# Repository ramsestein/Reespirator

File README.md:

# Reespirator 2020

Este repositorio pretende documentar y organizar los pasos para fabricar prototipos de  **Reespirator-2020**, un respirador open-source basado en el sistema de ventilación mecánica Jackson-Rees, diseñado y mejorado a partir de los prototipos elaborados por el equipo de Reesistencia Team para todas aquellas personas, organizaciones o empresas que quieran fabricarlo en cualquier parte del mundo.  

> ESTA DOCUMENTACIÓN ESTÁ EN ELABORACIÓN, COMPRUEBE REGULARMENTE LOS CAMBIOS, LAS PRIMERAS VERSIONES PUBLICADAS ESTÁN DESACTUALIZADAS. 

## Disclaimer
*Recuerde que un respirador es un dispositivo médico que sólo puede ser utilizado por personal cualificado y que un mal respirador o un respirador mal utilizado puede matar.*

La presente documentación **NO PERMITE CONSTRUIR UN RESPIRADOR FINAL**, sólo se publica para que se pueda fabricar PROTOTIPOS para investigación. 

## Info
*¿Qué es Reespirator 2020?*

El dispositivo Reespirator 2020 es un prototipo de sistema respirador de emergencia con elementos disponibles por la mayoría de las personas en cualquier parte del mundo, de rápida construcción y con la capacidad para mantener constantes ventilatorias aceptables en un paciente afecto de [Síndrome de Distrés Respiratorio Agudo](https://es.wikipedia.org/wiki/S%C3%ADndrome_de_dificultad_respiratoria_aguda) o SDRA que esperamos puede ser aplicable a los pacientes con COVID-19.

Aunque el origen de Reespirator es España, debido a las regulaciones y validaciones necesarias para los productos médicos, y aunque Reespirator 23 de [Reesistencia Team](https://gitlab.com/reesistencia), en el que se basó inicialmente este nuevo diseño, ha superado varias pruebas preclínicas con animales, y de compatibilidad electromagnética, suponemos que este dispositivo nunca se llegará a fabricar masivamente en España, dónde afortunadamente lo peor de la crisis del COVID-19 parece que ya ha pasado (08/04/20); esperamos que este y otros diseños puedan ser útiles en otros países.

Aún así no nos damos por vencidos y seguiremos desarrollando el proyecto al menos en 2 versiones:

* Versión low cost (basada en Arduino y con caja de metacrilato, madera...)
* Versión pro (con un autómata PLC + un HMI y caja de chapa plegada en acero inoxidable)

En la siguiente figura podemos ver una representación del dispositivo:

## Primeros pasos
**Antes de montar un respirador lea toda la documentación posible e infórmese bien, si necesita alguna aclaración abra un Issue y lo corregiremos en cuanto podamos. Si cree que puede mejorar el diseño, el código o que falta alguna cosa importante envíenos un Pull Request.**

## [Información médica básica del dispositivo Reespirator 2020](https://gitlab.com/reespirator/reespirator2020/-/blob/master/medical/MEDICAL.md)
El dispositivo se está diseñando para intentar cumplir las siguientes [especificaciones clínicas](https://foro.coronavirusmakers.org/index.php?p=/discussion/44/especificaciones-clinicas-de-un-respirador-util-en-esta-crisis#latest). Los dispositivos que estamos prototipando podrán funcionar en diferentes modos ventilatorios. En el siguiente enlace tendrás acceso a [Información médica básica sobre el dispositivo Reespirator 2020](https://gitlab.com/reespirator/reespirator2020/-/blob/master/medical/MEDICAL.md)

## [Estructura básica](https://gitlab.com/reespirator/reespirator2020/-/blob/master/case/CASE.md)
La versión low-cost de Reespirator 2020 consta de una [caja](https://gitlab.com/reespirator/reespirator2020/-/blob/master/case/CASE.md) diseñada para fabricarse mediante corte láser que contiene casi todos elementos del respirador en su interior. En el prototipo actual las piezas del prototipo se han diseñado para su corte por láser en metacrilato, si bien la imagen anterior corresponde a la nueva evolución que podrá fabricarse también con chapa plegada.

## [Sistema neumático](https://gitlab.com/reespirator/reespirator2020/-/blob/master/neumatic/NEUMATIC.md)
El [sistema neumático](https://gitlab.com/reespirator/reespirator2020/-/blob/master/neumatic/NEUMATIC.md) del Reespirator 2020 está basado en un sistema Jackson-Rees. Reespirator 2020 utiliza además una serie de válvulas, sensores de presión y caudal y tubuladuras para hacer llegar al aire a los pulmones del paciente.

## [Mecánica](https://gitlab.com/reespirator/reespirator2020/-/blob/master/mechanic/MECHANIC.md)
El [sistema mecánico](https://gitlab.com/reespirator/reespirator-doc/-/blob/master/mechanic/MECHANIC.md) pretende realizar los movimientos necesarios para realizar las maniobras de inspiración y espiración forzada del paciente mediante elementos mecánicos sustituyendo al personal humano que utilizaría el sistema de ventilación.

## [Electrónica](https://gitlab.com/reespirator/reespirator2020/-/blob/master/electronics/ELECTRONICS.md)
La [electrónica](https://gitlab.com/reespirator/reespirator-doc/-/blob/master/electronics/ELECTRONICS.md) de control gestiona el movimiento del motor y los sensores que permiten realizar un control de lazo cerrado automatizado del sistema.
Además de la electrónica de control se emplea una electrónica adicional como interfaz de usuario que permite monitorizar diferentes señales del respirador y modificar en tiempo real diferentes configuraciones del mismo.

## [Firmware](https://gitlab.com/reespirator/reespirator-doc/-/blob/master/firmware/FIRMWARE.md)
El sistema de control necesita ser programado con un [firmware](https://gitlab.com/reespirator/reespirator-doc/-/blob/master/firmware/FIRMWARE.md) que permita hacer funcionar el dispositivo. Dicho programa se ha realizado conforme a las especificaciones de los especialistas médicos para realizar las funciones para las que el dispositivo fue diseñado.

## [Simulación](https://gitlab.com/reespirator/reespirator2020/-/blob/master/simulation/SIMULATION.md)
En este apartado se consideran los fundamentos del sistema de control en lazo cerrado para los distintos modos de control que permite el Reespirator 2020. Los modelos matemáticos que permiten la [simulación numérica](https://gitlab.com/reespirasistemator/reespirator2020/-/blob/master/simulation/SIMULATION.md) del comportamiento del sistema corresponden a la información de este apartado.

## [Lista de materiales](https://gitlab.com/reespirator/reespirator2020/-/blob/master/bom/BOM.md)
La [lista de materiales, (BOM o Bill of materials)](https://gitlab.com/reespirator/reespirator2020/-/blob/master/bom/BOM.md) para construir un Reespirator 2020 es cuando menos complicada, incluye elementos como metacrilato, madera, MDF o chapa para la caja, sistmeas electrónicos como un Arduino Mega o un autómata PLC, y otros componentes, pero también elementos mecánicos y otros incluso impresos en 3D; pero sobre todo requiere también de la utilización de sistemas médicos tales como tubuladuras y un sistema ventilatorio Jackson-Rees.

## [Manual de usuario](https://gitlab.com/reespirator/reespirator2020/-/blob/master/manual/MANUAL.md)
El dispositivo Reespirator 2020 es un dispositivo médico y su uso sólo debe realizarse por personal especializado. Ofrecemos aquí un breve [manual de uso](https://gitlab.com/reespirator/reespirator-doc/-/blob/master/manual/MANUAL.md) del mismo; pero es el personal sanitario el que sabe los parámetros que deben utilizarse para el tratamiento de un paciente.

## [Vídeos]
En el siguiente enlace podemos ver algunos vídeos con detalles del Reespirator 2020 en funcionamiento:

* https://www.youtube.com/channel/UC9xr1HbWGLBjd4ADTvGcOnw

## Historia y principales cambios de esta versión

El proyecto Reespirator2020 toma como punto de partida el proyecto Reespirator 23 (o 24) v3 de **Reesistencia Team** a partir del cual realizamos un fork, el repositorio original está en [https://gitlab.com/reesistencia](https://gitlab.com/reesistencia).

En esta nueva versión se incluyen principalmente los siguientes cambios:

 - Revisión y reestructuración en profundidad del códido de Arduino para asegurar la robustez de funcionamiento en todos los supuestos.
 - La recuperación del interfaz básico con LCD de 20x04 y elementos sencillos de control (4 pulsadores y un encoder con pulsador).
 - Establecimiento y documentación de una interfaz de comunicación serie que permite la utilización de sistemas (en adelante llamados Display+) de visualización, control y conectividad, que pueden ser utilizados como accesorios para aportar mejor usabilidad al sistema.
 - Se trabaja para estandarizar y popularizar los sensores y electro-válvulas para utilizar partes (comerciales o diseñadas) posibles de conseguir con la situación de emergencia actual y a precios accesibles.
 - Posibilidad de usar diferentes interfaces de usuario.
 - Opción de utilizar un microcontrolador tipo Arduino o similar o bien un autómata PLC.

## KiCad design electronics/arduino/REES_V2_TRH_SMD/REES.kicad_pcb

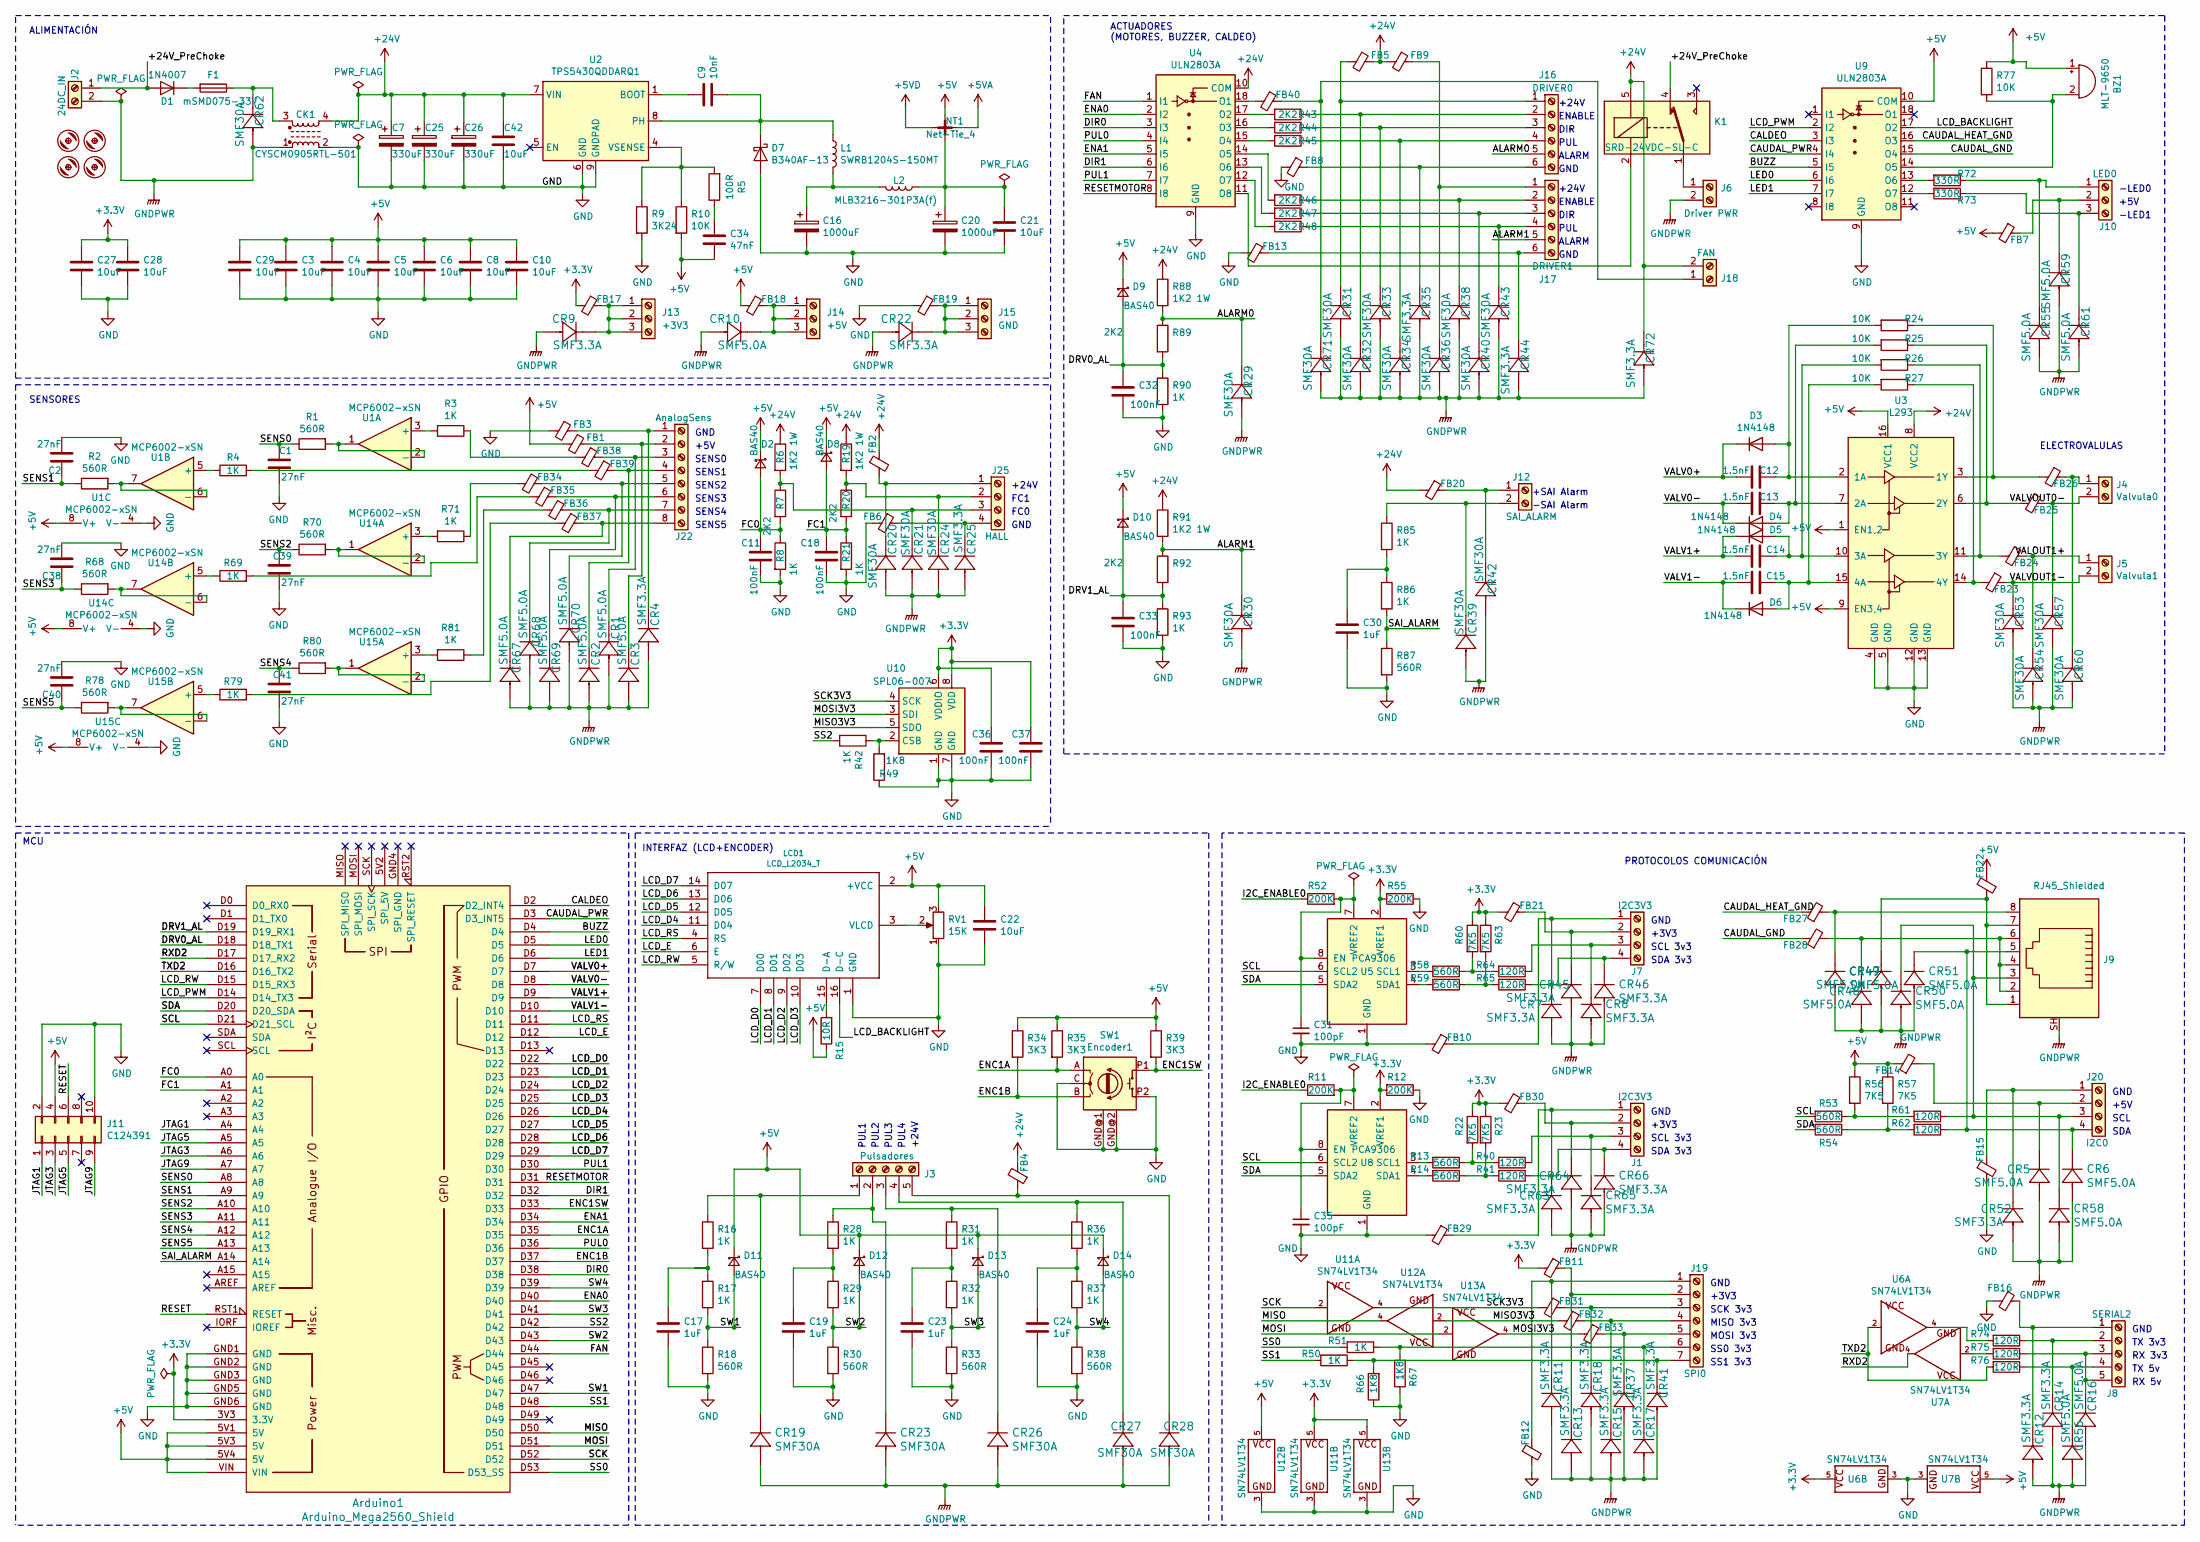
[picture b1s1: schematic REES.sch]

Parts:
Arduino1: Arduino_Mega2560_Shield
BZ1: MLT-9650; Buzzer_CUI_CPT-9019S-SMT
C1, C2, C38, C39, C40, C41: 27nF; C_0603_1608Metric
C3, C4, C5, C6, C8, C10, C21, C22, C27, C28, C29, C42: 10uF; C_1206_3216Metric
C7, C25, C26: 330uF; CP_Elec_10x10.5
C9: 10nF; C_0603_1608Metric
C11, C18, C32, C33, C36, C37: 100nF; C_0603_1608Metric
C12, C13, C14, C15: 1.5nF; C_0603_1608Metric
C16, C20: 1000uF; CP_Elec_10x10.5
C17, C19, C23, C24, C30: 1uF; C_0603_1608Metric
C31, C35: 100pF; C_0603_1608Metric
C34: 47nF; C_0603_1608Metric
CK1: CYSCM0905RTL-501; L_CommonMode_Wuerth_WE-SL2
CR1, CR2, CR3, CR5, CR6, CR10, CR16, CR47, CR48, CR49, CR50, CR51, CR55, CR56, CR58, CR59, CR61, CR67, CR68, CR69, CR70: SMF5.0A; D_SOD-123F
CR4, CR7, CR8, CR9, CR11, CR12, CR13, CR14, CR15, CR17, CR18, CR22, CR25, CR35, CR37, CR41, CR44, CR45, CR46, CR52, CR63, CR64, CR65, CR66, CR72: SMF3.3A; D_SOD-123F
CR19, CR20, CR21, CR23, CR24, CR26, CR27, CR28, CR29, CR30, CR31, CR32, CR33, CR34, CR36, CR38, CR39, CR40, CR42, CR43, CR53, CR54, CR57, CR60, CR62, CR71: SMF30A; D_SOD-123F
D1: 1N4007; D_SMA
D2, D8, D9, D10, D11, D12, D13, D14: BAS40; D_SOT-23_ANK
D3, D4, D5, D6: 1N4148; D_SOD-123
D7: B340AF-13; D_SMA
F1: mSMD075-33V; Fuse_1812_4532Metric
FB1, FB2, FB3, FB4, FB5, FB6, FB7, FB8, FB9, FB10, FB11, FB12, FB13, FB14, FB15, FB16, FB17, FB18, FB19, FB20, FB21, FB22, FB23, FB24, FB25, FB26, FB27, FB28, FB29, FB30, FB31, FB32, FB33, FB34, FB35, FB36, FB37, FB38, FB39, FB40: MLB3216-301P3A(f); C_1206_3216Metric
H1, H2, H3, H4: HOLES_MOUNT-HOLE3.6; HOLES_3,6
J1, J7: I2C3V3; TerminalBlock_Phoenix_MKDS-3-4-5.08_1x04_P5.08mm_Horizontal
J2: 24DC_IN; TerminalBlock_Phoenix_MKDS-3-2-5.08_1x02_P5.08mm_Horizontal
J3: Pulsadores; TerminalBlock_Phoenix_MKDS-3-5-5.08_1x05_P5.08mm_Horizontal
J4: Valvula0; TerminalBlock_Phoenix_MKDS-3-2-5.08_1x02_P5.08mm_Horizontal
J5: Valvula1; TerminalBlock_Phoenix_MKDS-3-2-5.08_1x02_P5.08mm_Horizontal
J6: Driver PWR; TerminalBlock_Phoenix_MKDS-3-2-5.08_1x02_P5.08mm_Horizontal
J8: SERIAL2; TerminalBlock_Phoenix_MKDS-3-5-5.08_1x05_P5.08mm_Horizontal
J9: RJ45_Shielded; RJ45_Hanrun_HR911105A
J10: LED0; TerminalBlock_Phoenix_MKDS-3-3-5.08_1x03_P5.08mm_Horizontal
J11: C124391; PinHeader_2x05_P2.54mm_Vertical_SMD
J12: SAI_ALARM; TerminalBlock_Phoenix_MKDS-3-2-5.08_1x02_P5.08mm_Horizontal
J13: +3V3; TerminalBlock_Phoenix_MKDS-3-3-5.08_1x03_P5.08mm_Horizontal
J14: +5V; TerminalBlock_Phoenix_MKDS-3-3-5.08_1x03_P5.08mm_Horizontal
J15: GND; TerminalBlock_Phoenix_MKDS-3-3-5.08_1x03_P5.08mm_Horizontal
J16: DRIVER0; TerminalBlock_Phoenix_MKDS-3-6-5.08_1x06_P5.08mm_Horizontal
J17: DRIVER1; TerminalBlock_Phoenix_MKDS-3-6-5.08_1x06_P5.08mm_Horizontal
J18: FAN; TerminalBlock_Phoenix_MKDS-3-2-5.08_1x02_P5.08mm_Horizontal
J19: SPI0; TerminalBlock_Phoenix_MKDS-3-7-5.08_1x07_P5.08mm_Horizontal
J20: I2C0; TerminalBlock_Phoenix_MKDS-3-4-5.08_1x04_P5.08mm_Horizontal
J22: AnalogSens; TerminalBlock_Phoenix_MKDS-3-8-5.08_1x08_P5.08mm_Horizontal
J25: HALL; TerminalBlock_Phoenix_MKDS-3-4-5.08_1x04_P5.08mm_Horizontal
K1: SRD-24VDC-SL-C; Relay_SPDT_Omron-G5LE-1
L1: SWRB1204S-150MT; L_Bourns_SRR1210A
L2: MLB3216-301P3A(f); C_1206_3216Metric
LCD1: LCD_L2034_T; L2034-T
NT1: Net-Tie_4; NetTie-4_SMD_Pad0.5mm
R1, R2, R13, R14, R18, R30, R33, R38, R53, R54, R58, R59, R68, R70, R78, R80, R87: 560R; R_0805_2012Metric
R3, R4, R8, R16, R17, R21, R28, R29, R31, R32, R36, R37, R42, R50, R51, R69, R71, R79, R81, R85, R86, R90, R93: 1K; R_1206_3216Metric
R5: 100R; R_0805_2012Metric
R6, R19, R88, R91: 1K2 1W; R_2512_6332Metric
R7, R20, R43, R44, R45, R46, R47, R48, R89, R92: 2K2; R_1206_3216Metric
R9: 3K24; R_0603_1608Metric
R10, R77: 10K; R_0603_1608Metric
R11, R12, R52, R55: 200K; R_0603_1608Metric
R15: 10R; R_1206_3216Metric
R22, R23, R56, R57, R60, R63: 7K5; R_0603_1608Metric
R24, R25, R26, R27: 10K; R_0805_2012Metric
R34, R35: 3K3; R_0603_1608Metric
R39: 3K3; R_0805_2012Metric
R40, R41, R61, R62, R64, R65, R74, R75, R76: 120R; R_1206_3216Metric
R49, R66, R67: 1K8; R_1206_3216Metric
R72, R73: 330R; R_0805_2012Metric
RV1: 15K; Potentiometer_Bourns_3214W_Vertical
SW1: Encoder1; PEC12_INCREMENTAL_ENCODER
U1, U14, U15: MCP6002-xSN; SOIC-8_3.9x4.9mm_P1.27mm
U2: TPS5430QDDARQ1; TI_SO-PowerPAD-8_ThermalVias
U3: L293; DIP-16_W7.62mm
U4, U9: ULN2803A; SOIC-18W_7.5x11.6mm_P1.27mm
U5, U8: PCA9306; TSSOP-8_3x3mm_P0.65mm
U6, U7, U11, U12, U13: SN74LV1T34; SOT-23-5_HandSoldering
U10: SPL06-007; Bosch_LGA-8_2x2.5mm_P0.65mm_ClockwisePinNumbering

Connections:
+3V3: Arduino1.3V3 (3.3V), C27.1, C28.1, C36.1, C37.1, FB11.2, FB17.2, FB21.2, FB30.2, R12.2, R22.1, R23.1, R55.2, R60.1, R63.1, U5.2 (VREF1), U6.5 (P$V+), U8.2 (VREF1), U10.6 (VDDIO), U10.8 (VDD), U11.5 (P$V+), U13.5 (P$V+)
+5V: Arduino1.5V1 (5V), Arduino1.5V3 (5V), Arduino1.5V4 (5V), Arduino1.VIN, BZ1.1 (-), C3.1, C4.1, C5.1, C6.1, C8.1, C10.1, C22.1, C29.1, C34.2, D2.1 (K), D8.1 (K), D9.1 (K), D10.1 (K), D11.1 (K), D12.1 (K), D13.1 (K), D14.1 (K), FB1.2, FB7.2, FB14.1, FB18.2, FB22.1, J11.4, LCD1.2 (+VCC), NT1.3, R10.2, R15.1, R34.1, R35.1, R39.1, R56.1, R57.1, R77.1, RV1.3, U1.8 (V+), U3.1 (EN1,2), U3.9 (EN3,4), U3.16 (VCC1), U7.5 (P$V+), U9.10 (COM), U12.5 (P$V+), U14.8 (V+), U15.8 (V+)
+24V: C7.1, C25.1, C26.1, C42.1, CK1.4, CR72.1, FB2.1, FB4.2, FB5.1, FB9.2, FB20.2, J18.2, K1.5, R6.1, R19.1, R88.1, R91.1, U2.7 (VIN), U3.8 (VCC2), U4.10 (COM)
/+24V_PreChoke: D1.2 (A), J2.1, K1.4
/ALARM0: CR29.1, J16.5, R88.2, R89.1
/ALARM1: CR30.1, J17.5, R91.2, R92.1
/BUZZ: Arduino1.D4, U9.5 (I5)
/CALDEO: Arduino1.D2 (D2_INT4), U9.3 (I3)
/CAUDAL_GND: FB28.1, U9.15 (O4)
/CAUDAL_HEAT_GND: FB27.1, U9.16 (O3)
/CAUDAL_PWR: Arduino1.D3 (D3_INT5), U9.4 (I4)
/DIR0: Arduino1.D38, U4.3 (I3)
/DIR1: Arduino1.D32, U4.6 (I6)
/DRV0_AL: Arduino1.D18 (D18_TX1), C32.1, D9.2 (A), R89.2, R90.1
/DRV1_AL: Arduino1.D19 (D19_RX1), C33.1, D10.2 (A), R92.2, R93.1
/ENA0: Arduino1.D40, U4.2 (I2)
/ENA1: Arduino1.D34, U4.5 (I5)
/ENC1A: Arduino1.D35, R35.2, SW1.A
/ENC1B: Arduino1.D37, R34.2, SW1.B
/ENC1SW: Arduino1.D33, R39.2, SW1.P1
/FAN: Arduino1.D44, U4.1 (I1)
/FC0: Arduino1.A0, C11.1, D2.2 (A), R7.2, R8.1
/FC1: Arduino1.A1, C18.1, D8.2 (A), R20.2, R21.1
/I2C_ENABLE0: R11.1, R52.1
/JTAG1: Arduino1.A4, J11.1
/JTAG3: Arduino1.A6, J11.3
/JTAG5: Arduino1.A5, J11.5
/JTAG9: Arduino1.A7, J11.9
/LCD_BACKLIGHT: LCD1.16 (D-C), U9.17 (O2)
/LCD_D0: Arduino1.D22, LCD1.7 (D00)
/LCD_D1: Arduino1.D23, LCD1.8 (D01)
/LCD_D2: Arduino1.D24, LCD1.9 (D02)
/LCD_D3: Arduino1.D25, LCD1.10 (D03)
/LCD_D4: Arduino1.D26, LCD1.11 (D04)
/LCD_D5: Arduino1.D27, LCD1.12 (D05)
/LCD_D6: Arduino1.D28, LCD1.13 (D06)
/LCD_D7: Arduino1.D29, LCD1.14 (D07)
/LCD_E: Arduino1.D12, LCD1.6 (E)
/LCD_PWM: Arduino1.D14 (D14_TX3), U9.2 (I2)
/LCD_RS: Arduino1.D11, LCD1.4 (RS)
/LCD_RW: Arduino1.D15 (D15_RX3), LCD1.5 (R/W)
/LED0: Arduino1.D5, U9.6 (I6)
/LED1: Arduino1.D6, U9.7 (I7)
/MISO: Arduino1.D50, U12.4 (Y)
/MISO3V3: FB32.2, U10.5 (SDO), U12.2 (A)
/MOSI: Arduino1.D51, U13.2 (A)
/MOSI3V3: FB33.2, U10.3 (SDI), U13.4 (Y)
/PUL0: Arduino1.D36, U4.4 (I4)
/PUL1: Arduino1.D30, U4.7 (I7)
/RESET: Arduino1.RST1 (RESET), J11.6
/RESETMOTOR: Arduino1.D31, U4.8 (I8)
/RXD2: Arduino1.D17 (D17_RX2), U7.4 (Y)
/SAI_ALARM: Arduino1.A14, R86.2, R87.1
/SCK: Arduino1.D52, U11.2 (A)
/SCK3V3: FB31.2, U10.4 (SCK), U11.4 (Y)
/SCL: Arduino1.D21 (D21_SCL), R53.2, U5.6 (SCL2), U8.6 (SCL2)
/SDA: Arduino1.D20 (D20_SDA), R54.2, U5.5 (SDA2), U8.5 (SDA2)
/SENS0: Arduino1.A8, C1.1, R1.1
/SENS1: Arduino1.A9, C2.1, R2.1
/SENS2: Arduino1.A10, C39.1, R70.1
/SENS3: Arduino1.A11, C38.1, R68.1
/SENS4: Arduino1.A12, C41.1, R80.1
/SENS5: Arduino1.A13, C40.1, R78.1
/SS0: Arduino1.D53 (D53_SS), R51.2
/SS1: Arduino1.D48, R50.2
/SS2: Arduino1.D42, R42.2
/SW1: Arduino1.D47, D11.2 (A), R17.2, R18.1
/SW2: Arduino1.D43, D12.2 (A), R29.2, R30.1
/SW3: Arduino1.D41, D13.2 (A), R32.2, R33.1
/SW4: Arduino1.D39, D14.2 (A), R37.2, R38.1
/TXD2: Arduino1.D16 (D16_TX2), R76.2, U6.2 (A)
/VALOUT1+: CR54.1, FB24.1, J5.1
/VALV0+: Arduino1.D7, C12.2, D3.1 (K)
/VALV0-: Arduino1.D8, C13.2, D4.1 (K)
/VALV1+: Arduino1.D9, C14.2, D5.1 (K)
/VALV1-: Arduino1.D10, C15.2, D6.1 (K)
/VALVOUT0-: CR57.1, FB25.1, J4.2
/VALVOUT1-: CR53.1, FB23.1, J5.2
GND: Arduino1.GND1 (GND), Arduino1.GND2 (GND), Arduino1.GND3 (GND), Arduino1.GND5 (GND), Arduino1.GND6 (GND), C1.2, C2.2, C3.2, C4.2, C5.2, C6.2, C7.2, C8.2, C10.2, C11.2, C16.2, C17.2, C18.2, C19.2, C20.2, C21.2, C22.2, C23.2, C24.2, C25.2, C26.2, C27.2, C28.2, C29.2, C30.2, C31.2, C32.2, C33.2, C35.2, C36.2, C37.2, C38.2, C39.2, C40.2, C41.2, C42.2, CK1.2, D7.2 (A), FB3.2, FB6.2, FB8.2, FB10.2, FB12.2, FB13.2, FB15.2, FB16.2, FB19.2, FB29.2, J11.2, J11.10, LCD1.1 (GND), R8.2, R9.2, R12.1, R18.2, R21.2, R30.2, R33.2, R38.2, R49.1, R55.1, R66.1, R67.1, R87.2, R90.2, R93.2, RV1.1, SW1.C, SW1.GND@1, SW1.GND@2, SW1.P2, U1.4 (V-), U2.6 (GND), U2.9 (GNDPAD), U3.4 (GND), U3.5 (GND), U3.12 (GND), U3.13 (GND), U4.9 (GND), U5.1 (GND), U6.3 (P$V-), U7.3 (P$V-), U8.1 (GND), U9.9 (GND), U10.1 (GND), U10.7 (GND), U11.3 (P$V-), U12.3 (P$V-), U13.3 (P$V-), U14.4 (V-), U15.4 (V-)
GNDPWR: CK1.1, CR1.2, CR2.2, CR3.2, CR4.2, CR5.2, CR6.2, CR7.2, CR8.2, CR9.2, CR10.2, CR11.2, CR12.2, CR13.2, CR14.2, CR15.2, CR16.2, CR17.2, CR18.2, CR19.2, CR20.2, CR21.2, CR22.2, CR23.2, CR24.2, CR25.2, CR26.2, CR27.2, CR28.2, CR29.2, CR30.2, CR31.2, CR32.2, CR33.2, CR34.2, CR35.2, CR36.2, CR37.2, CR38.2, CR39.2, CR40.2, CR41.2, CR42.2, CR43.2, CR44.2, CR45.2, CR46.2, CR47.2, CR48.2, CR49.2, CR50.2, CR51.2, CR52.2, CR53.2, CR54.2, CR55.2, CR56.2, CR57.2, CR58.2, CR59.2, CR60.2, CR61.2, CR62.2, CR63.2, CR64.2, CR65.2, CR66.2, CR67.2, CR68.2, CR69.2, CR70.2, CR71.2, CR72.2, J2.2, J6.2, J9.SH
unnamed: BZ1.2 (+), R77.2, U9.14 (O5)
unnamed: C9.1, U2.1 (BOOT)
unnamed: C9.2, D7.1 (K), L1.1, U2.8 (PH)
unnamed: C12.1, D3.2 (A), R24.2, U3.2 (1A)
unnamed: C13.1, D4.2 (A), R25.2, U3.7 (2A)
unnamed: C14.1, D5.2 (A), R26.2, U3.10 (3A)
unnamed: C15.1, D6.2 (A), R27.2, U3.15 (4A)
unnamed: C16.1, L1.2, L2.2
unnamed: C17.1, R16.2, R17.1
unnamed: C19.1, R28.2, R29.1
unnamed: C20.1, C21.1, L2.1, NT1.4
unnamed: C23.1, R31.2, R32.1
unnamed: C24.1, R36.2, R37.1
unnamed: C30.1, R85.2, R86.1
unnamed: C31.1, R52.2, U5.7 (VREF2), U5.8 (EN)
unnamed: C34.1, R5.1
unnamed: C35.1, R11.2, U8.7 (VREF2), U8.8 (EN)
unnamed: CK1.3, CR62.1, F1.1
unnamed: CR1.1, FB38.1, J22.3
unnamed: CR2.1, FB39.1, J22.4
unnamed: CR3.1, FB1.1, J22.2
unnamed: CR4.1, FB3.1, J22.1
unnamed: CR5.1, FB14.2, J20.2
unnamed: CR8.1, J7.3, R64.1
unnamed: CR9.1, FB17.1, J13.1, J13.2, J13.3
unnamed: CR10.1, FB18.1, J14.1, J14.2, J14.3
unnamed: CR11.1, FB12.1, J19.1
unnamed: CR12.1, FB16.1, J8.1
unnamed: CR13.1, FB11.1, J19.2
unnamed: CR14.1, J8.2, R74.1
unnamed: CR15.1, FB32.1, J19.4
unnamed: CR16.1, J8.3, J8.5, R75.1
unnamed: CR17.1, J19.6, R51.1, R67.2
unnamed: CR18.1, FB31.1, J19.3
unnamed: CR19.1, J3.1, R16.1
unnamed: CR20.1, FB2.2, J25.1
unnamed: CR21.1, J25.3, R6.2, R7.1
unnamed: CR22.1, FB19.1, J15.1, J15.2, J15.3
unnamed: CR23.1, J3.2, R28.1
unnamed: CR24.1, J25.2, R19.2, R20.1
unnamed: CR25.1, FB6.1, J25.4
unnamed: CR26.1, J3.3, R31.1
unnamed: CR27.1, J3.4, R36.1
unnamed: CR28.1, FB4.1, J3.5
unnamed: CR31.1, FB5.2, J16.1
unnamed: CR32.1, J16.2, R43.1
unnamed: CR33.1, J16.3, R44.1
unnamed: CR34.1, J16.4, R45.1
unnamed: CR35.1, FB8.1, J16.6
unnamed: CR36.1, FB9.1, J17.1
unnamed: CR37.1, FB33.1, J19.5
unnamed: CR38.1, J17.2, R46.1
unnamed: CR39.1, J12.2, R85.1
unnamed: CR40.1, J17.3, R47.1
unnamed: CR41.1, J19.7, R50.1, R66.2
unnamed: CR42.1, FB20.1, J12.1
unnamed: CR43.1, J17.4, R48.1
unnamed: CR44.1, FB13.1, J17.6
unnamed: CR45.1, FB21.1, J7.2
unnamed: CR7.1, CR46.1, FB10.1, J7.1, J7.4, R65.1
unnamed: CR47.1, FB27.2, J9.8
unnamed: CR48.1, FB28.2, J9.2, J9.4, J9.6
unnamed: CR49.1, FB22.2, J9.1, J9.7
unnamed: CR50.1, CR58.1, J9.3, J20.3, R61.1
unnamed: CR6.1, CR51.1, J9.5, J20.4, R62.1
unnamed: CR52.1, FB15.1, J20.1
unnamed: CR55.1, J10.1, R72.1
unnamed: CR56.1, J8.4, R76.1
unnamed: CR59.1, FB7.1, J10.2
unnamed: CR60.1, FB26.1, J4.1
unnamed: CR61.1, J10.3, R73.1
unnamed: CR63.1, CR66.1, FB29.1, J1.1, J1.4, R41.1
unnamed: CR64.1, FB30.1, J1.2
unnamed: CR65.1, J1.3, R40.1
unnamed: CR67.1, FB37.1, J22.8
unnamed: CR68.1, FB36.1, J22.7
unnamed: CR69.1, FB35.1, J22.6
unnamed: CR70.1, FB34.1, J22.5
unnamed: CR71.1, FB40.1, J18.1
unnamed: D1.1 (K), F1.2
unnamed: FB23.2, R27.1, U3.14 (4Y)
unnamed: FB24.2, R26.1, U3.11 (3Y)
unnamed: FB25.2, R25.1, U3.6 (2Y)
unnamed: FB26.2, R24.1, U3.3 (1Y)
unnamed: FB34.2, R71.1
unnamed: FB35.2, R69.2
unnamed: FB36.2, R81.1
unnamed: FB37.2, R79.2
unnamed: FB38.2, R3.1
unnamed: FB39.2, R4.2
unnamed: FB40.2, U4.18 (O1)
unnamed: J6.1, K1.1
unnamed: K1.2, U4.11 (O8)
unnamed: LCD1.3 (VLCD), RV1.2
unnamed: LCD1.15 (D-A), R15.2
unnamed: R1.2, U1.1, U1.2 (-)
unnamed: R2.2, U1.6 (-), U1.7
unnamed: R3.2, U1.3 (+)
unnamed: R4.1, U1.5 (+)
unnamed: R5.2, R9.1, R10.1, U2.4 (VSENSE)
unnamed: R13.1, R22.2, R40.2
unnamed: R13.2, U8.3 (SCL1)
unnamed: R14.1, R23.2, R41.2
unnamed: R14.2, U8.4 (SDA1)
unnamed: R42.1, R49.2, U10.2 (CSB)
unnamed: R43.2, U4.17 (O2)
unnamed: R44.2, U4.16 (O3)
unnamed: R45.2, U4.15 (O4)
unnamed: R46.2, U4.14 (O5)
unnamed: R47.2, U4.13 (O6)
unnamed: R48.2, U4.12 (O7)
unnamed: R53.1, R56.2, R61.2
unnamed: R54.1, R57.2, R62.2
unnamed: R58.1, R60.2, R64.2
unnamed: R58.2, U5.3 (SCL1)
unnamed: R59.1, R63.2, R65.2
unnamed: R59.2, U5.4 (SDA1)
unnamed: R68.2, U14.6 (-), U14.7
unnamed: R69.1, U14.5 (+)
unnamed: R70.2, U14.1, U14.2 (-)
unnamed: R71.2, U14.3 (+)
unnamed: R72.2, U9.13 (O6)
unnamed: R73.2, U9.12 (O7)
unnamed: R74.2, U6.4 (Y)
unnamed: R75.2, U7.2 (A)
unnamed: R78.2, U15.6 (-), U15.7
unnamed: R79.1, U15.5 (+)
unnamed: R80.2, U15.1, U15.2 (-)
unnamed: R81.2, U15.3 (+)

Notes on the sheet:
ALIMENTACIÓN
ACTUADORES (MOTORES, BUZZER, CALDEO)
SENSORES
PROTOCOLOS COMUNICACIÓN
MCU
ELECTROVALULAS
RX 5v
TX 5v
TX 3v3
GND
-SAI Alarm
+SAI Alarm
RX 3v3
SCL 3v3
SDA 3v3
+3V3
SDA
+5V
SCL
PUL
ENABLE
+24V
DIR
ALARM
-LED0
-LED1
PUL3
PUL1
PUL2
PUL4
SCK 3v3
MISO 3v3
MOSI 3v3
SS0 3v3
SS1 3v3
SENS1
SENS0
FC0
FC1
INTERFAZ (LCD+ENCODER)

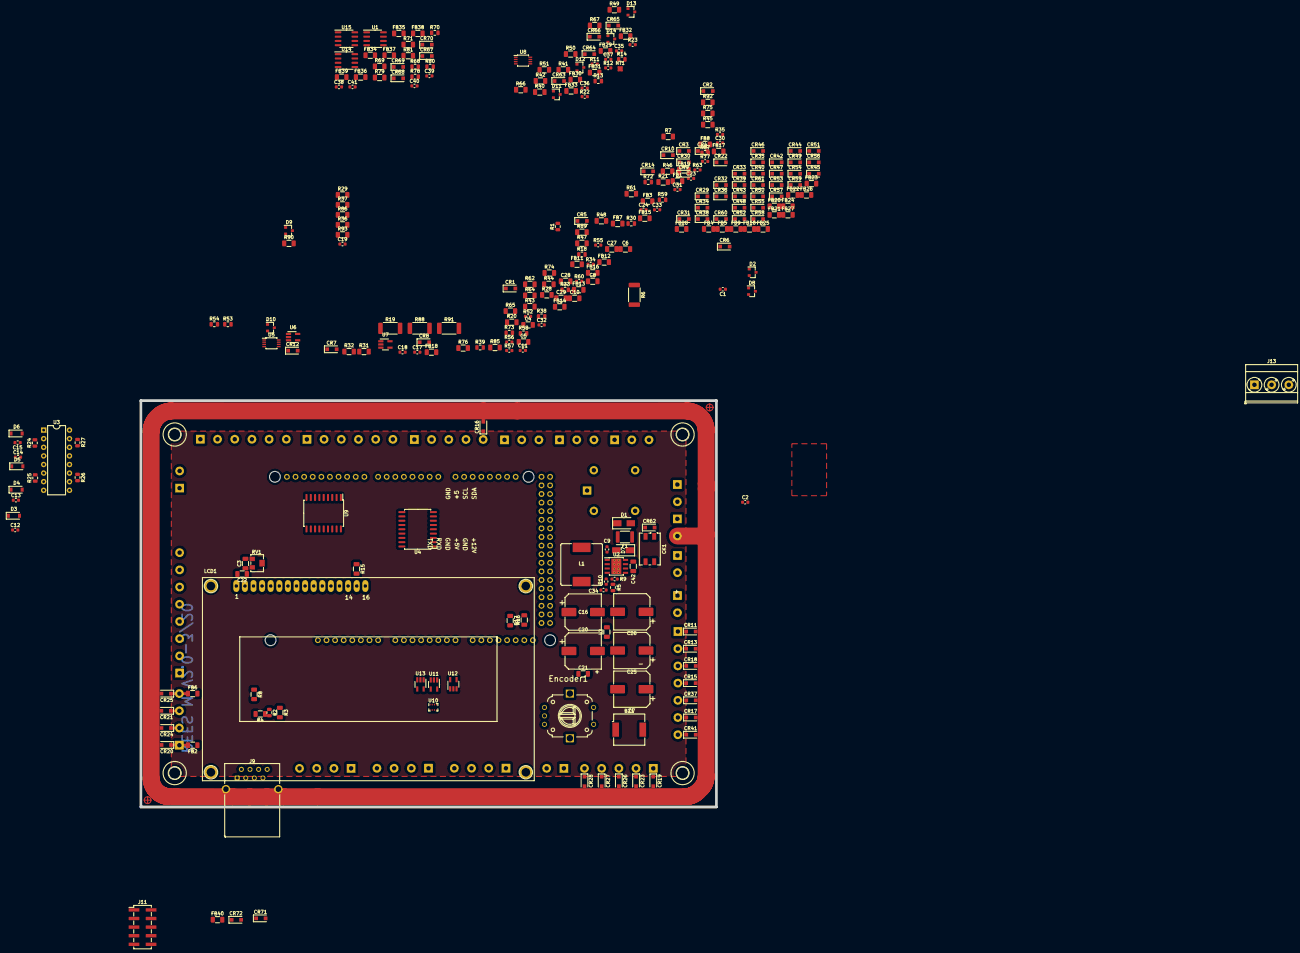
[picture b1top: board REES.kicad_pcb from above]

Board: 2 copper layers, 170.0 x 120.0 mm, 310 parts (0 on the bottom side), 209 nets.

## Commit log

2020-04-14 Update electronics/arduino/diagrama_bloques_esquema.md, images/diagrama_bloques_esquema.png, alimentacion_esquema.md, electronics/arduino/alimentacion_esquema.md, electronics/arduino/mcu_esquema.md, 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
2020-04-14 Montaje de la caja en metacrilato
2020-04-14 tapas para distintos tipos de pantallas
2020-04-15 organización de archivos de electrónica
2020-04-15 colocando archivos
2020-04-15 Comunicaciones e interfaces
2020-04-15 PCB files
2020-04-15 reorganize files
2020-04-15 move electronics
2020-04-15 Add new directory
2020-04-15 relocate files
2020-04-15 upload images and videos
2020-04-16 Planos de corte dxf y planos en Freecad de todas las piezas de metacrilato
2020-04-16 simulation
2020-04-17 Se adjunta la carpeta de archivos stp, se ha corregido la cuna ponindole 4 tornillos para sujetar a la base y se empieza las pruebas de la pala con pivote
2020-04-17 change images
2020-04-17 add new and change images
2020-04-17 change manual, medical and readme files
2020-04-17 update plc manual
2020-04-17 move images
2020-04-17 fix neumatic images
2020-04-18 mechanic update
2020-04-18 move md files to folders
2020-04-18 check sintax
2020-04-18 update stl images
2020-04-18 fix stl image path
2020-04-18 relocate images
2020-04-18 electronics images
2020-04-18 check files
2020-04-18 Manuales de reespirator 2020
2020-04-18 Add new file
2020-04-18 fix file name
2020-04-18 update medical info
2020-04-19 update interfaces files
2020-04-19 Update electronics/arduino/ARDUINO-ELECTRONICS.md, images/arduino/pinout_mcu.png files
2020-04-19 Upload New File
2020-04-19 Issue Rpi
2020-04-19 datasheets and manuals
2020-04-19 PLC BOM update
2020-04-19 new BOM update
2020-04-19 update interfaces
2020-04-21 Replace pinout_mcu.png
2020-04-21 Update images/arduino/esquema3DB.png, images/arduino/esquema3DF.png files
2020-04-26 Update electronics/arduino/interfaz_esquema.md, images/arduino/encoder.png, images/arduino/interfaz_esquema.png, images/arduino/lcd4x20.png files
2020-04-27 Se adjuntan piezas que faltaban como el acople motor y piezas nuevas en las que se esta trabajando
2020-04-30 Vídeos
2020-05-02 Update electronics/arduino/actuadores_esquema.md, images/arduino/actuadores_esquema.png, images/arduino/actuadores_esquema1.png, images/arduino/actuadores_esquema2.png, images/arduino/actuadores_esqu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
2020-05-02 Update images/arduino/pcb00.png, images/arduino/pcb01.png files
2020-05-04 Versión de Arduino para Reespirator 2020
2020-05-06 Se corregi un error en el archivo de corte de la pieza "Trasera"
2020-06-09 PLC firmware
2020-06-09 motor driver
